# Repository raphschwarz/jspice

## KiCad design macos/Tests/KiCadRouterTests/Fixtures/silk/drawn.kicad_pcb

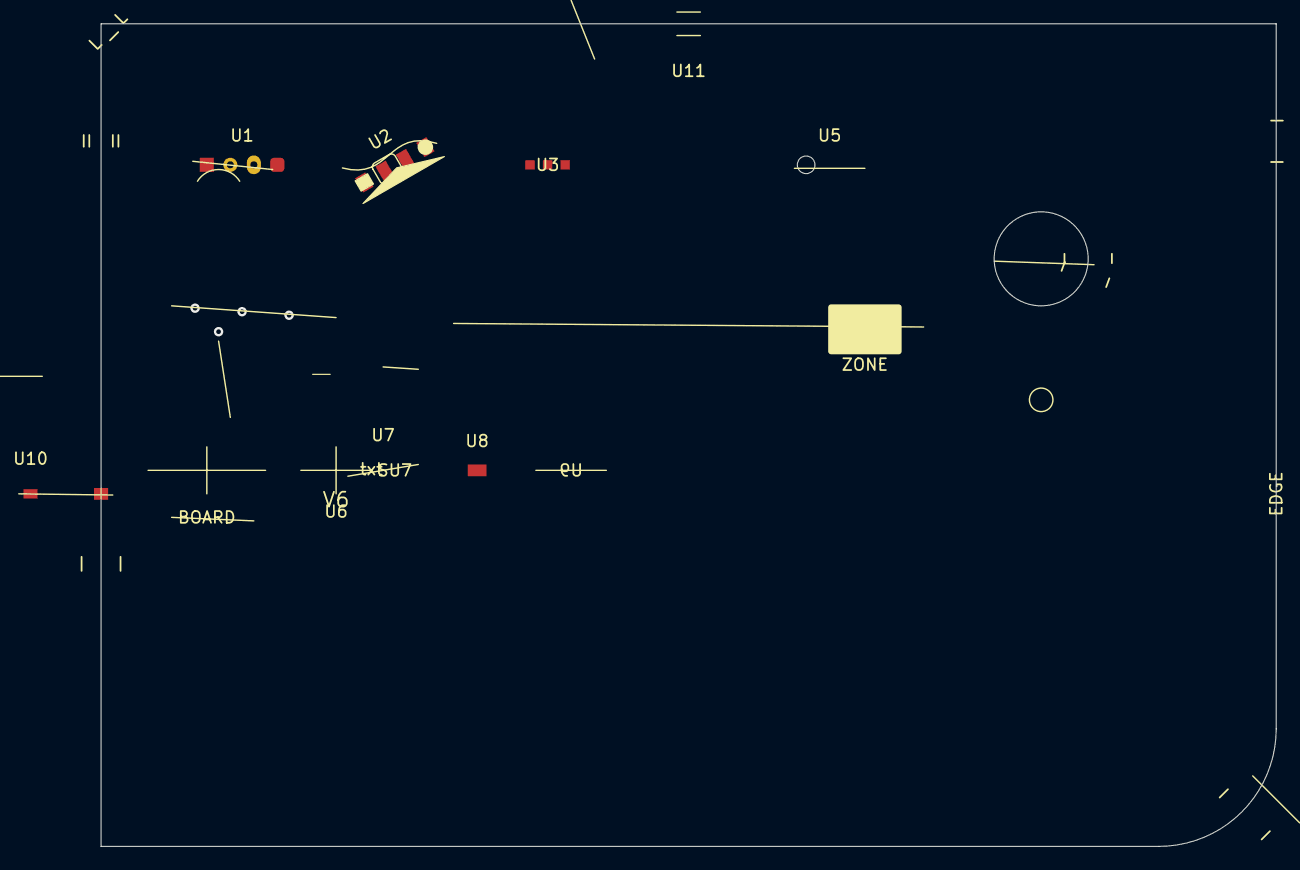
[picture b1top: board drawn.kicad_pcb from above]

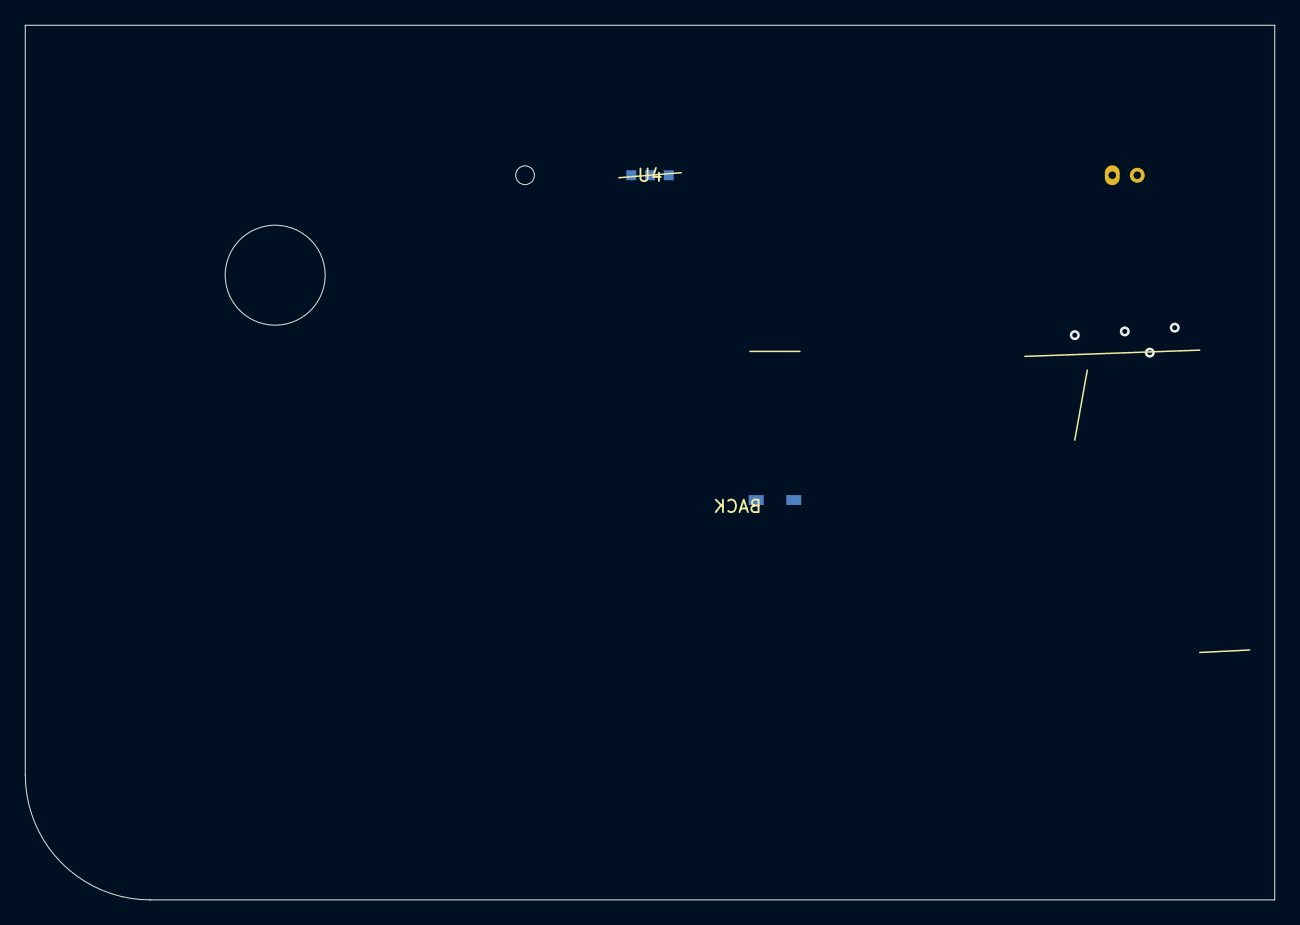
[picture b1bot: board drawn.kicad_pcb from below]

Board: 2 copper layers, 100.0 x 70.0 mm, 11 parts (2 on the bottom side), 2 nets.

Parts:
U1: V1
U2: V2
U3: V3
U4: V4
U5: V5
U6: V6
U7: V7
U8: V8
U9: V9
U10: V10
U11: V11

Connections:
GND: U2.2, U2.4, U9.2
SIG: U2.1, U2.3, U3.1, U3.2, U3.3, U4.1, U4.2, U4.3, U8.1, U9.1, U10.1, U10.2

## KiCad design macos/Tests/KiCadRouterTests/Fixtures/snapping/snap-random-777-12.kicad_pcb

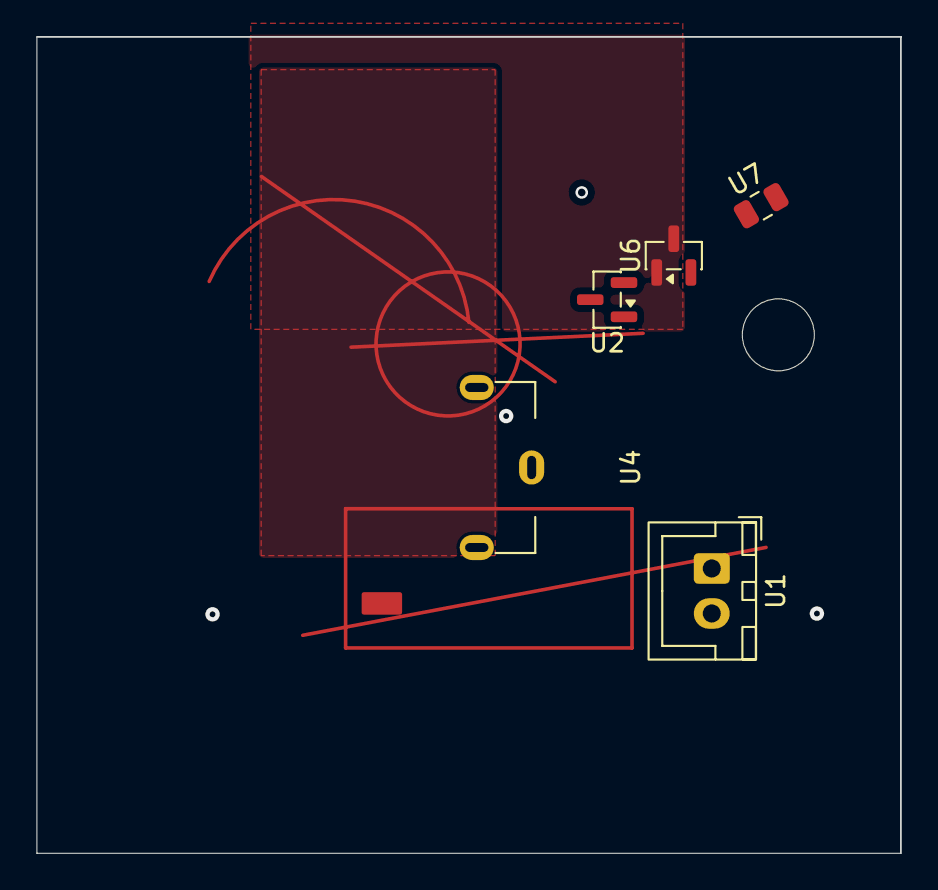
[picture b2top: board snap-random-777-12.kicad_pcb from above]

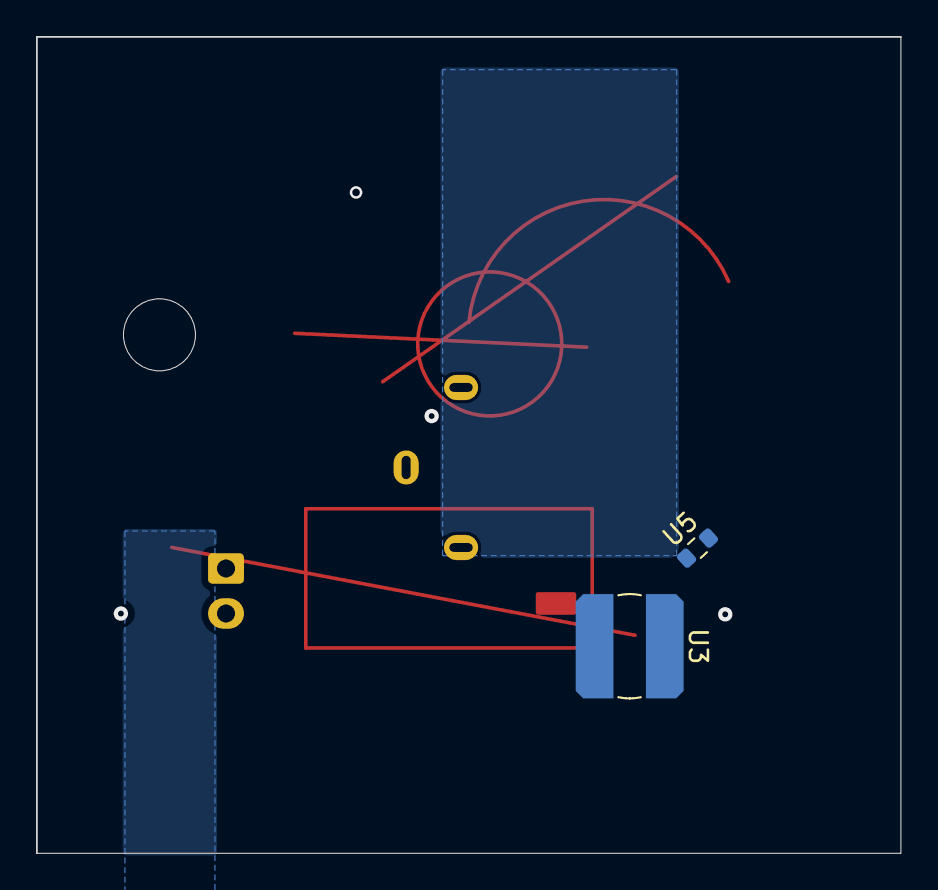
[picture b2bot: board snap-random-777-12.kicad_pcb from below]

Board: 2 copper layers, 48.0 x 45.4 mm, 7 parts (2 on the bottom side), 4 nets, no tracks yet.

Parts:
U1: JST_XH_B2B-XH-A_1x02_P2.50mm_Vertical
U2, U6: SOT-23
U3: L_Bourns_SDR0604
U4: BatteryHolder_Keystone_590
U5: R_0603_1608Metric
U7: C_0805_2012Metric

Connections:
/net3: U1.2, U5.2, U6.1
D7: U3.1, U7.2
D12: U2.3, U7.1
VCC: U2.1, U2.2

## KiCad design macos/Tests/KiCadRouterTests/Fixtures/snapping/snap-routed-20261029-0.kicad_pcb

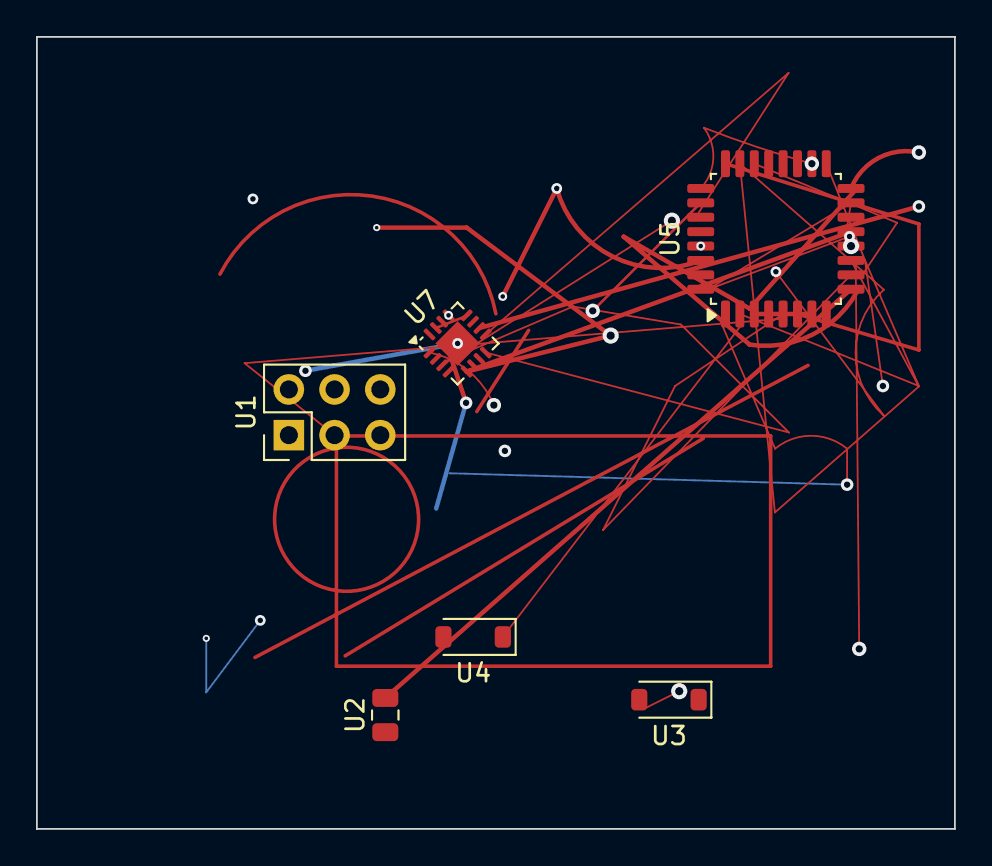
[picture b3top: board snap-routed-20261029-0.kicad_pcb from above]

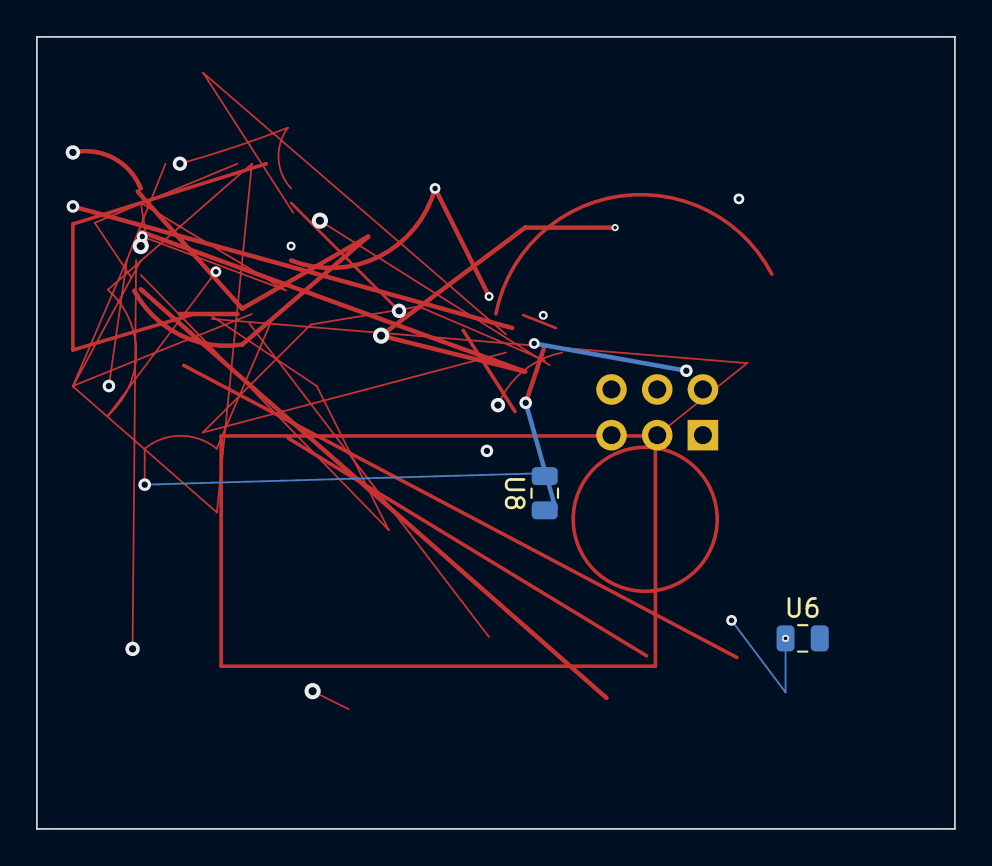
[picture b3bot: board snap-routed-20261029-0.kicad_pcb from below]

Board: 6 copper layers, 51.0 x 44.0 mm, 8 parts (2 on the bottom side), 10 nets.

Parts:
U1: PinHeader_2x03_P2.54mm_Vertical
U2, U6, U8: C_0805_2012Metric
U3, U4: D_SOD-123
U5: LQFP-32_7x7mm_P0.8mm
U7: QFN-16-1EP_3x3mm_P0.5mm_EP1.75x1.75mm

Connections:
4k7: U5.3, U5.7, U5.30, U7.2, U7.16
+3V3: U1.1, U1.5, U5.12, U5.15, U5.32, U7.3, U7.8
/sub/CLK2: U5.6, U5.24, U5.31
/sub/clk: U5.26, U5.29, U7.12, U7.15
D12: U4.1, U5.2, U5.17, U5.18, U5.25
unnamed: U3.1, U5.1, U8.2
R1: U2.2, U5.9, U5.16, U7.10
R10: U3.2, U5.11, U5.23, U6.1, U7.1
SIG10: U1.3, U5.5, U5.10, U5.22, U5.27, U7.9
VCC: U5.13, U7.5, U7.13, U7.17, U8.1

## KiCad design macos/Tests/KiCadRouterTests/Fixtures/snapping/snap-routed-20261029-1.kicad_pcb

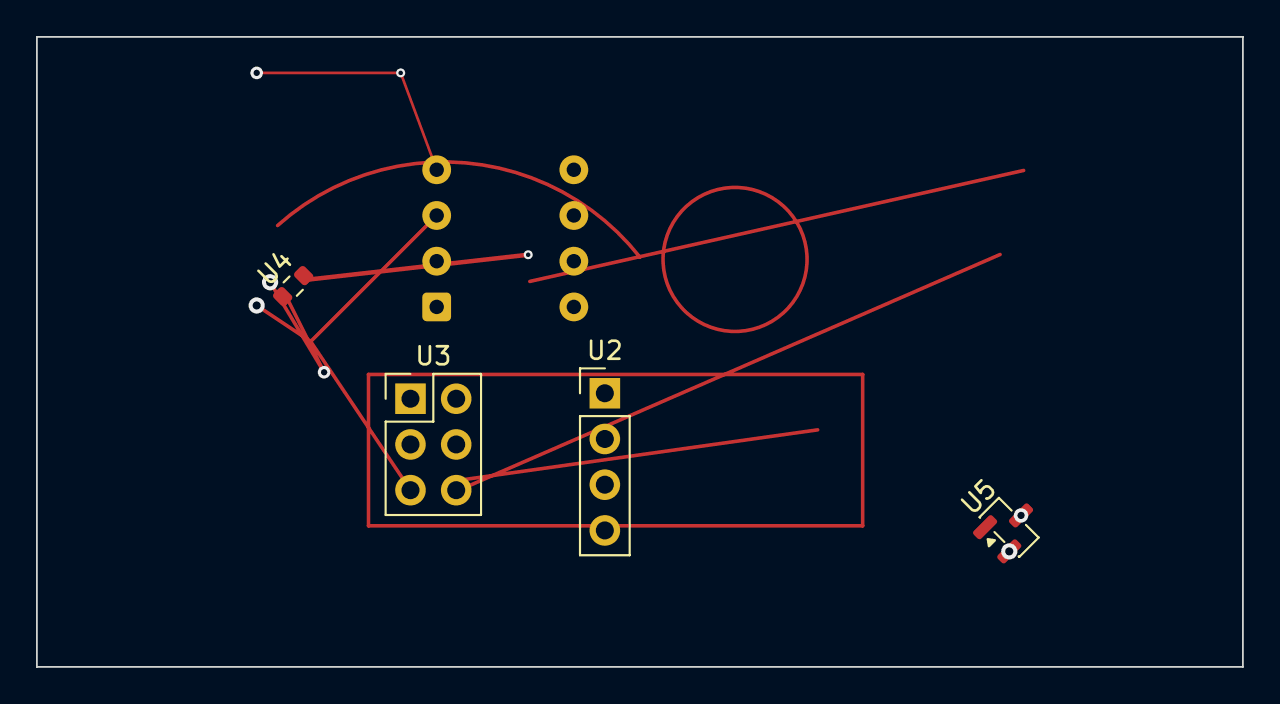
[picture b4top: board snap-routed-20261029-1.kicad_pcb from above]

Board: 6 copper layers, 67.0 x 35.0 mm, 5 parts (1 on the bottom side), 4 nets.

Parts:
U1: DIP-8_W7.62mm
U2: PinHeader_1x04_P2.54mm_Vertical
U3: PinHeader_2x03_P2.54mm_Vertical
U4: R_0603_1608Metric
U5: SOT-23

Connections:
4K7_IN: U1.4, U1.7, U2.3
D12: U1.1, U1.8
GND: U1.3, U3.5, U5.3
VCC: U4.1, U5.2

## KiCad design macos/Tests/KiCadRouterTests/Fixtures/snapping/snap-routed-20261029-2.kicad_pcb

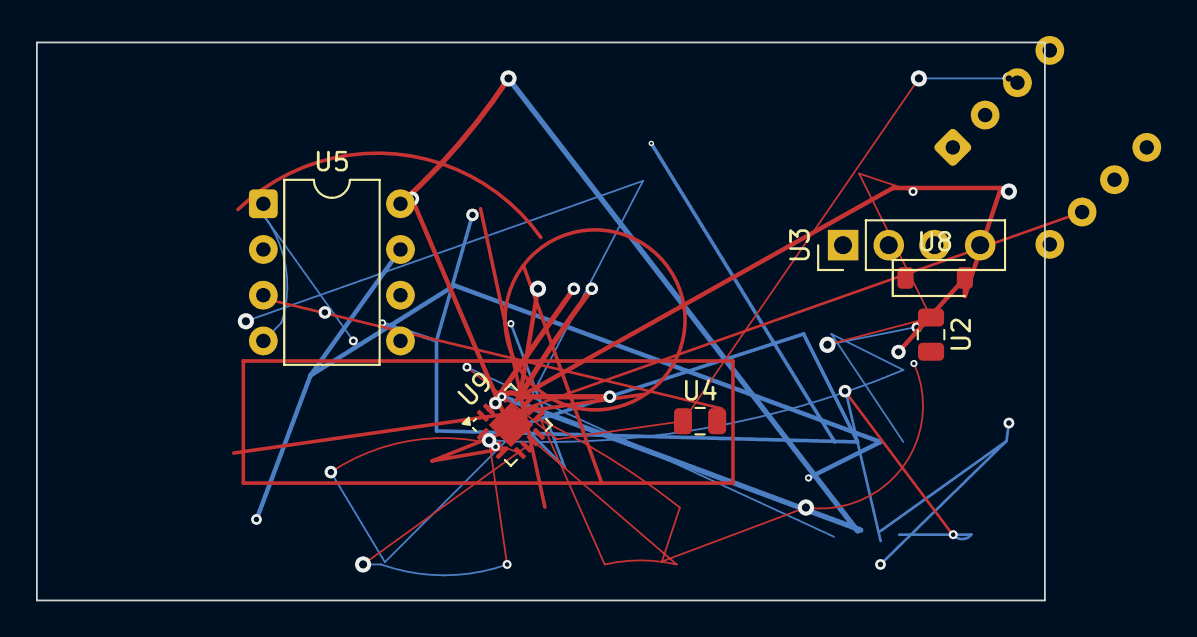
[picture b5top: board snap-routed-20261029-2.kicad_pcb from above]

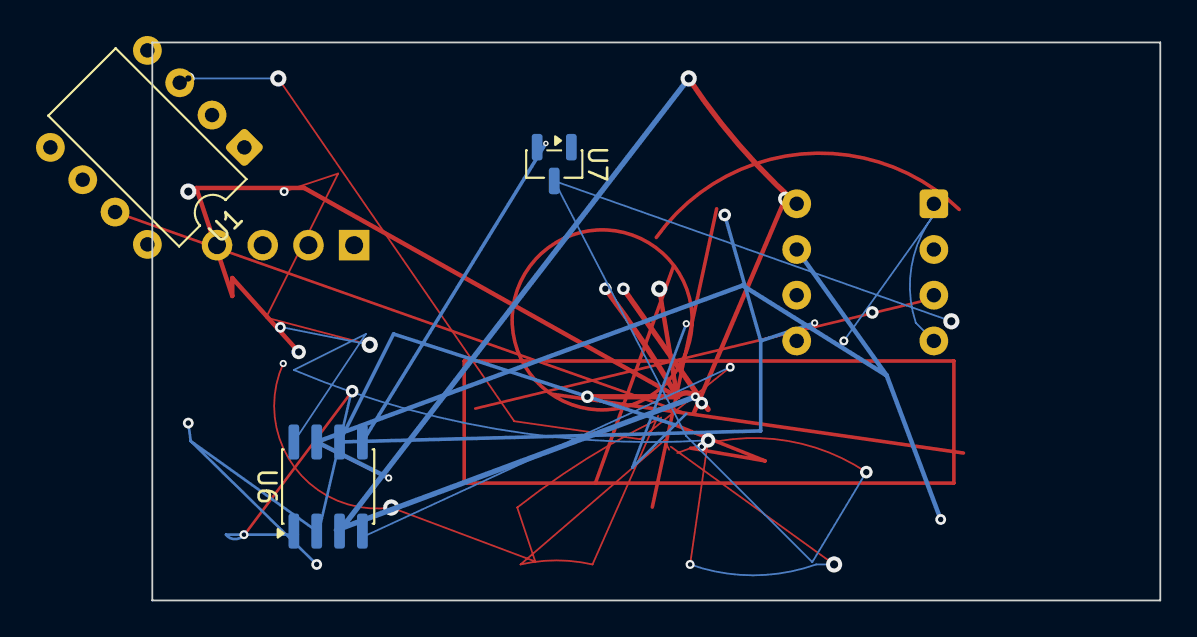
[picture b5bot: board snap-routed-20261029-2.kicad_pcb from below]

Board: 4 copper layers, 56.0 x 31.0 mm, 9 parts (3 on the bottom side), 8 nets.

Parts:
U1, U5: DIP-8_W7.62mm
U2, U4: C_0805_2012Metric
U3: PinHeader_1x04_P2.54mm_Vertical
U6: SOIC-8_3.9x4.9mm_P1.27mm
U7: SOT-23
U8: D_SOD-123
U9: QFN-16-1EP_3x3mm_P0.5mm_EP1.75x1.75mm

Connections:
/sub/clk: U1.8, U5.5, U6.5, U6.6, U9.4, U9.16
D7: U1.7, U9.3
GND: U1.5, U4.1, U6.4, U6.8, U9.2, U9.6, U9.7, U9.9, U9.14
PWR_5V: U2.2, U5.8, U6.3, U9.13, U9.15
R1: U1.3, U5.7, U6.7, U8.2, U9.12, U9.17
SIG10: U1.4, U1.6, U4.2, U5.3
VCC: U1.1, U2.1, U5.4, U7.3, U9.5
sig3: U6.1, U6.2

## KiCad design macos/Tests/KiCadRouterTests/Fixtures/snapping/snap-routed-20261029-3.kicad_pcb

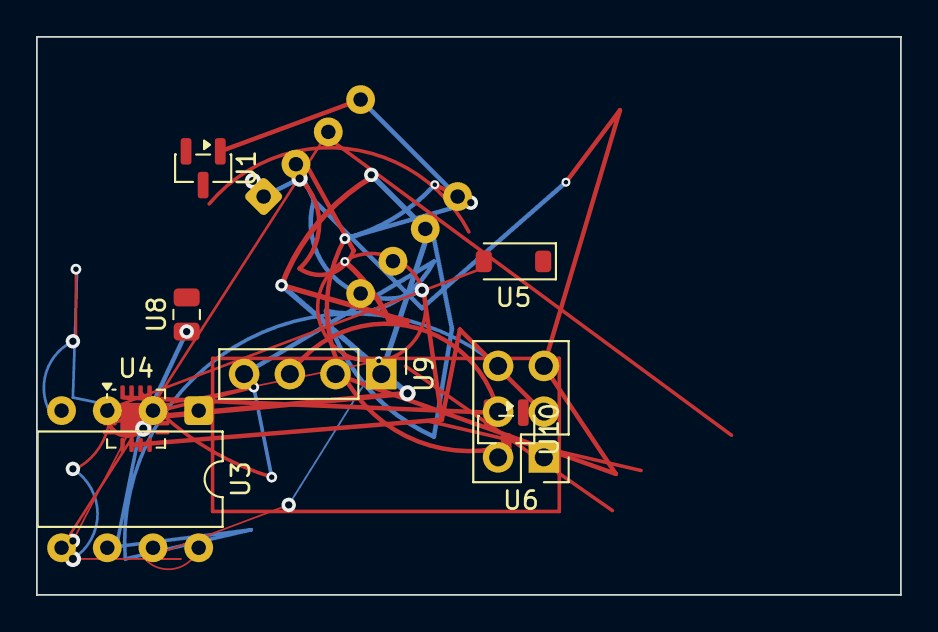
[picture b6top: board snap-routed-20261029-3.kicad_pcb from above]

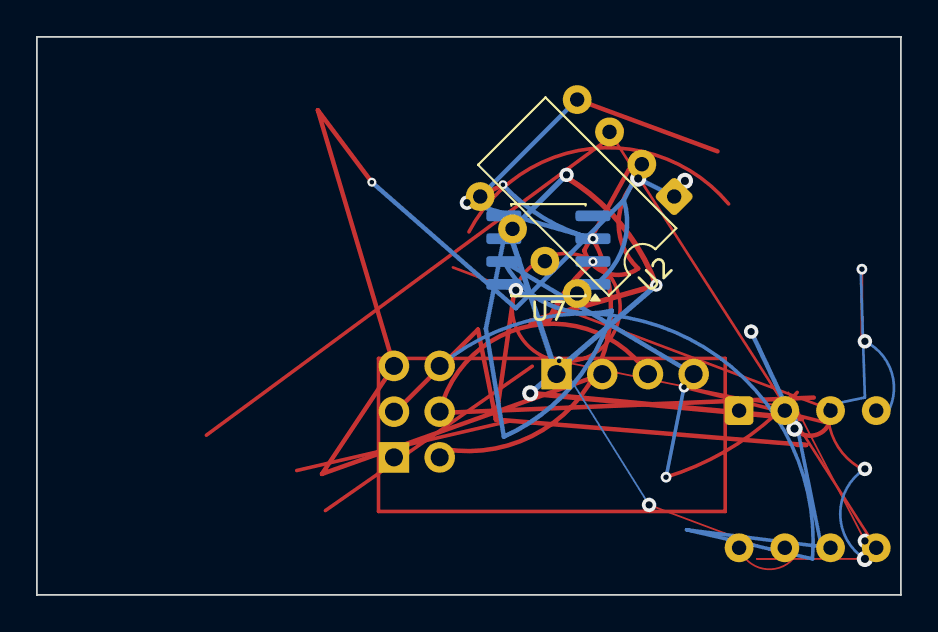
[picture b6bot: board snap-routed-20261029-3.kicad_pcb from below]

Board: 2 copper layers, 48.0 x 31.0 mm, 10 parts (2 on the bottom side), 11 nets.

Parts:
U1, U10: SOT-23
U2, U3: DIP-8_W7.62mm
U4: QFN-16-1EP_3x3mm_P0.5mm_EP1.75x1.75mm
U5: D_SOD-123
U6: PinHeader_2x03_P2.54mm_Vertical
U7: SOIC-8_3.9x4.9mm_P1.27mm
U8: C_0805_2012Metric
U9: PinHeader_1x04_P2.54mm_Vertical

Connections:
4K7_IN: U7.6, U7.7, U9.4
/sub/CLK2: U4.3, U4.14
/sub/clk: U1.3, U2.7, U7.4, U7.5, U9.1
D7: U7.3, U10.3
D12: U2.1, U2.2, U4.6, U4.7, U6.3, U6.5, U9.2
GND: U3.8, U4.12, U4.13
N2: U1.1, U2.4, U2.5, U4.16, U6.4, U9.3
unnamed: U3.4, U4.1, U5.2, U10.1
R10: U3.2, U3.6, U6.6, U10.2
SIG10: U3.3, U8.1
VCC: U2.6, U4.17, U7.2

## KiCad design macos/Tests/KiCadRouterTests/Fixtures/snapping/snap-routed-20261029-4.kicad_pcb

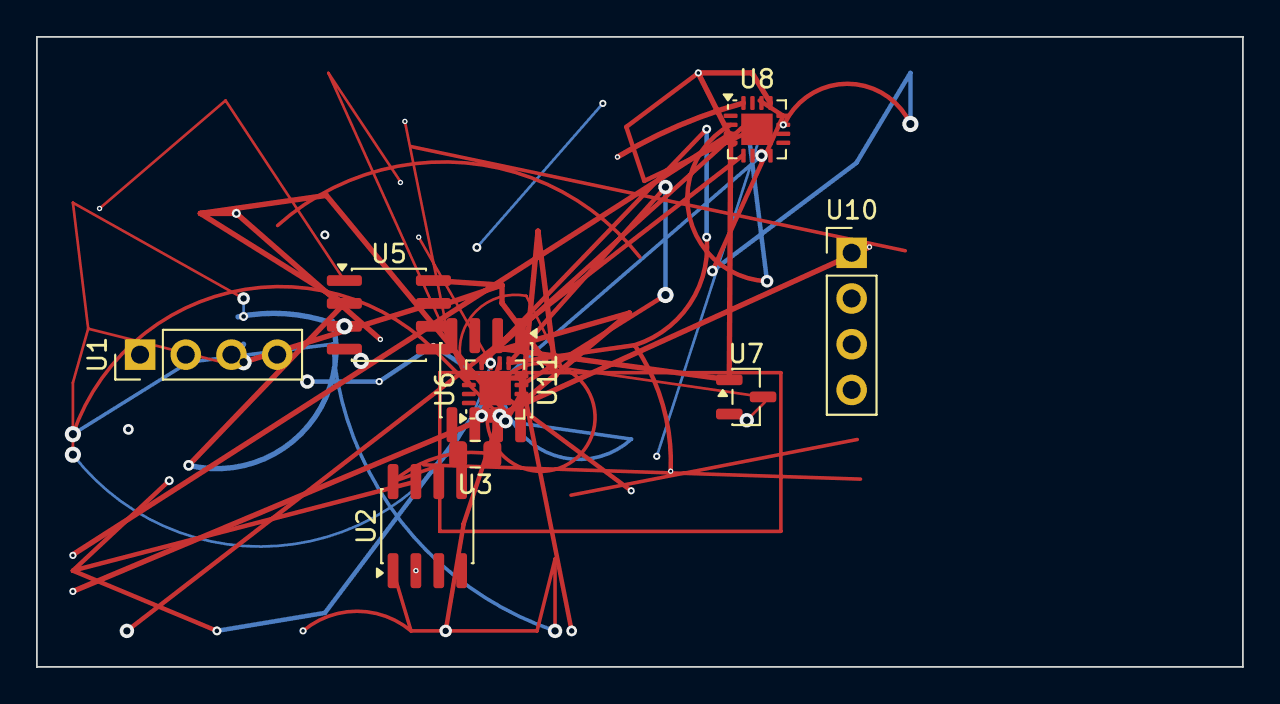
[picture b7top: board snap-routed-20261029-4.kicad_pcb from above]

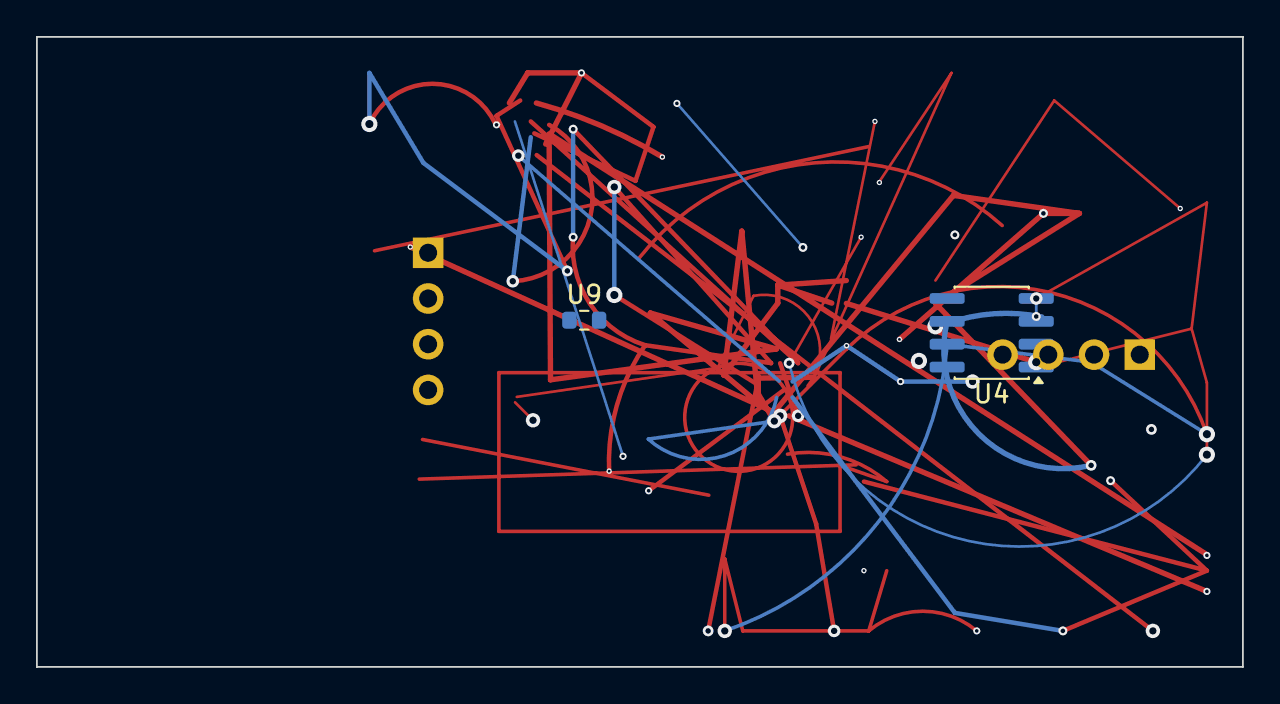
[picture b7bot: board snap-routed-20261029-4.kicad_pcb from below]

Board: 4 copper layers, 67.0 x 35.0 mm, 11 parts (2 on the bottom side), 6 nets.

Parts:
U1, U10: PinHeader_1x04_P2.54mm_Vertical
U2, U4, U5, U11: SOIC-8_3.9x4.9mm_P1.27mm
U3: C_0805_2012Metric
U6, U8: QFN-16-1EP_3x3mm_P0.5mm_EP1.75x1.75mm
U7: SOT-23
U9: R_0603_1608Metric

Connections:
4K7_IN: U1.4, U2.7, U6.3, U6.7, U6.9, U6.12, U8.2, U8.5, U8.8, U8.11, U8.12, U8.14, U9.1, U10.3
GND: U4.3, U4.6, U5.2, U5.3, U5.6, U6.2, U6.4, U6.6, U6.8, U6.13, U6.15, U8.3, U8.6, U8.16, U11.7
unnamed: U4.2, U5.7, U5.8, U6.5, U7.1, U8.4, U8.13, U11.3
R10: U6.1, U6.10, U6.17
SIG2: U1.1, U1.3, U4.4, U5.1, U6.11, U6.14, U7.3, U11.4
sig3: U1.2, U2.1, U2.2, U2.6, U2.8, U3.1, U4.7, U5.5, U8.7, U9.2
